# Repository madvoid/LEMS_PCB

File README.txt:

Eagle Files for LEMS PCB
Work in progress

The Mega Shield Schematic/Layout will be used as a reference in the future

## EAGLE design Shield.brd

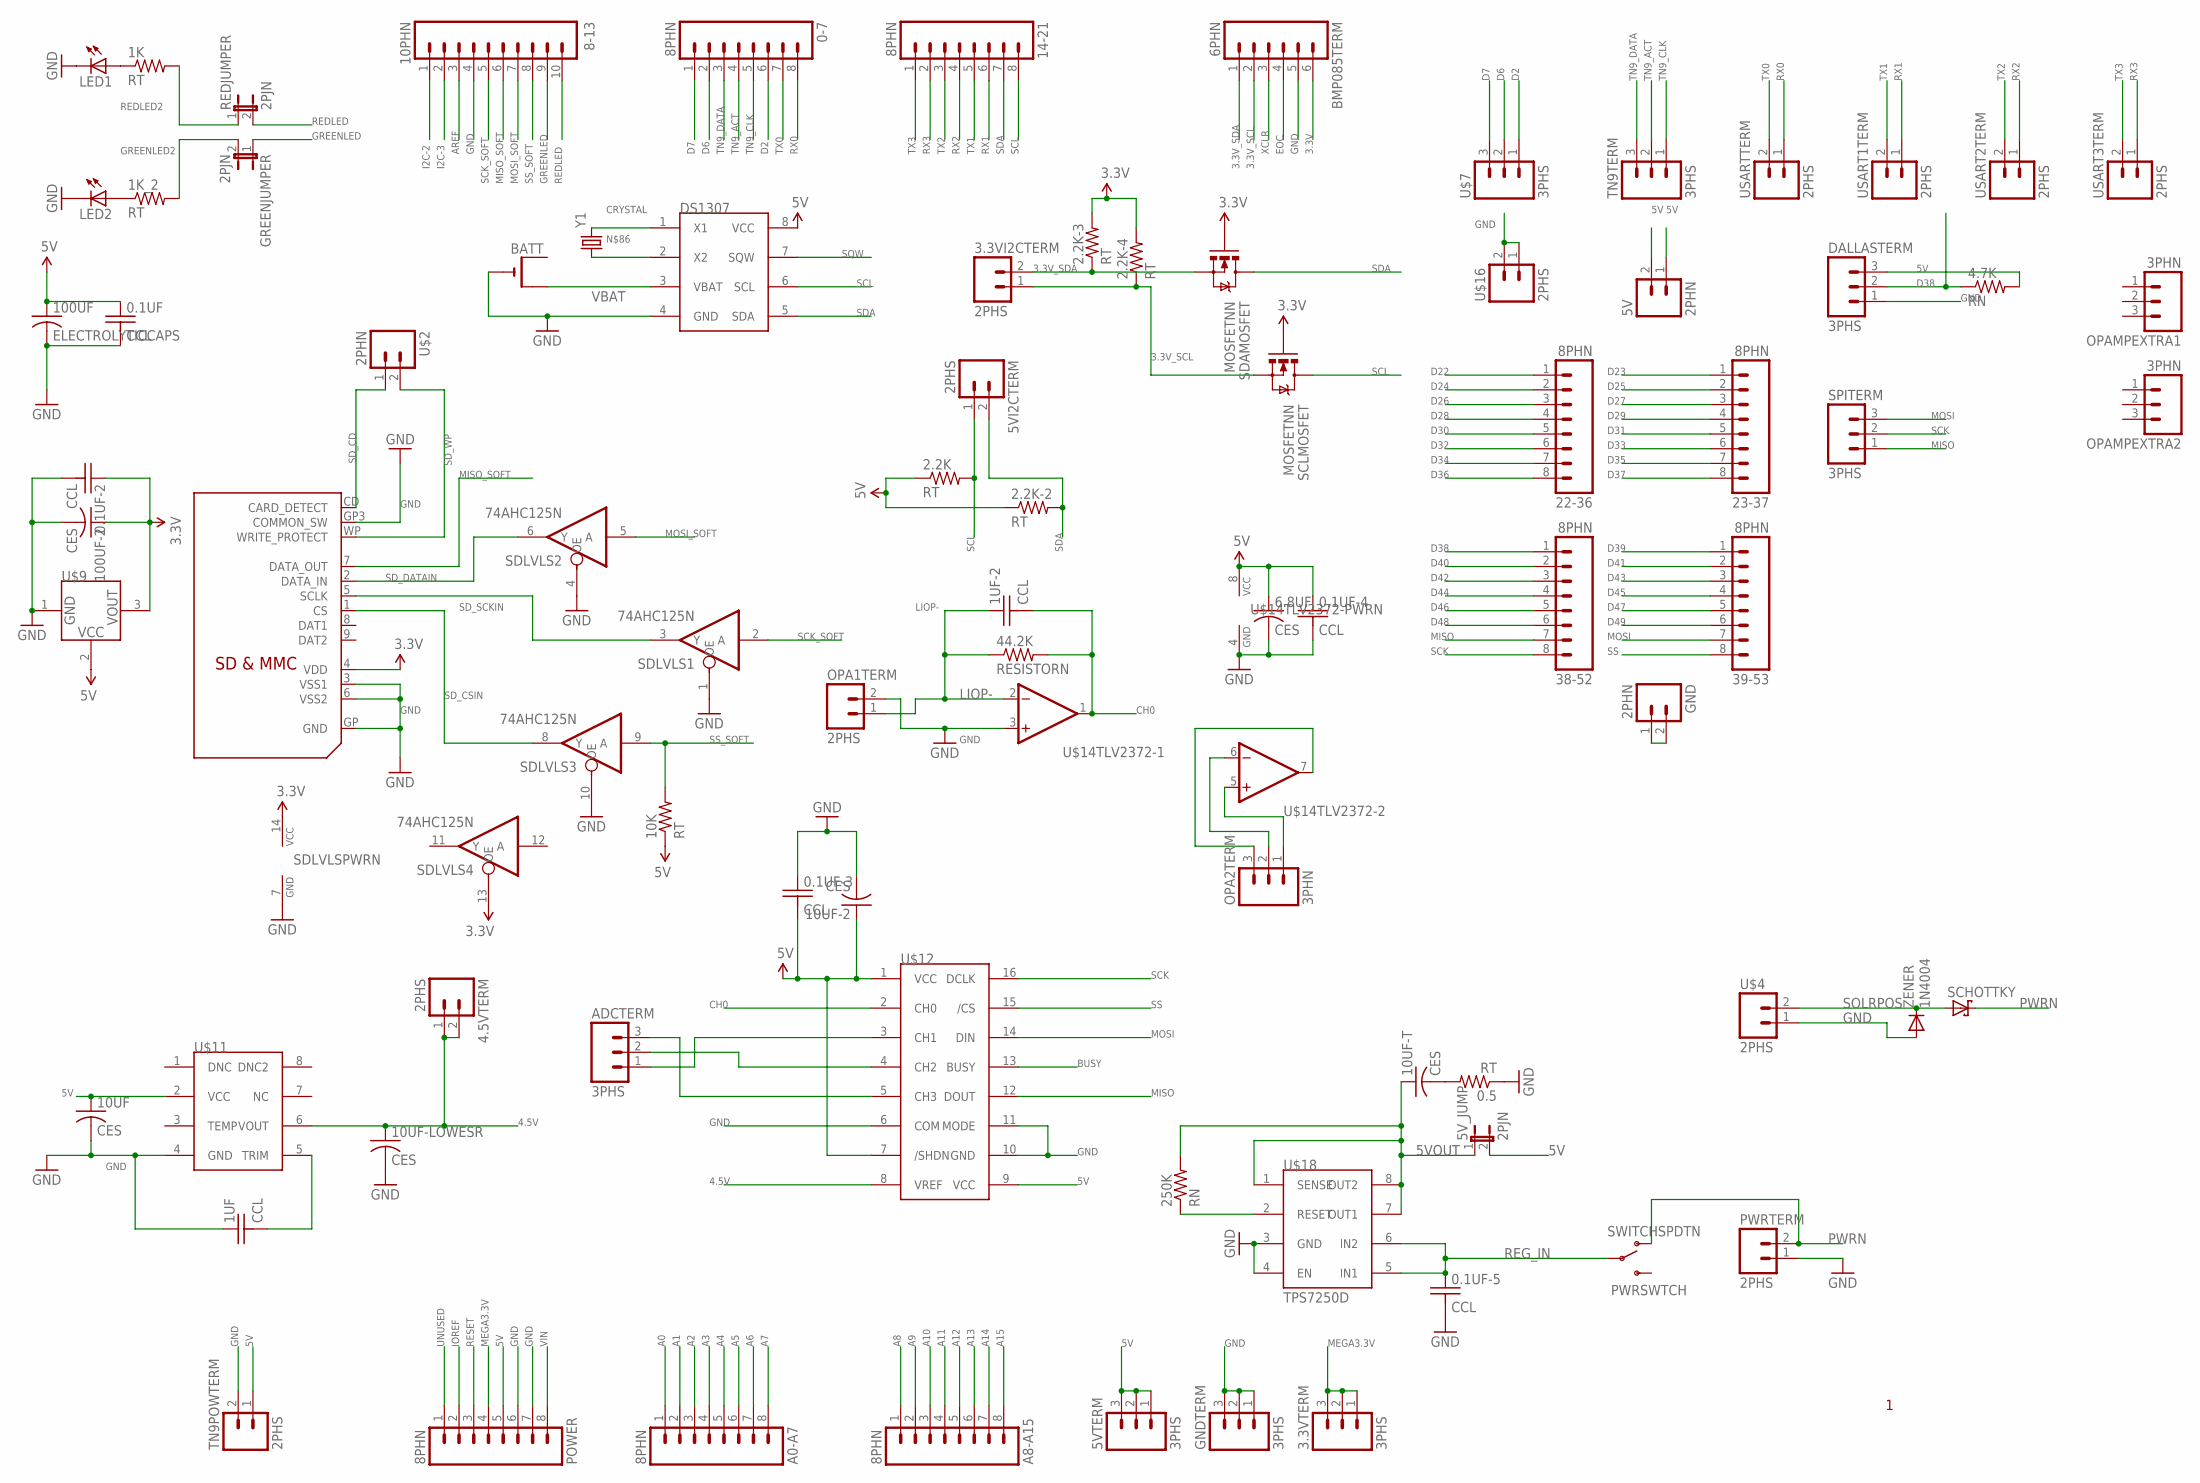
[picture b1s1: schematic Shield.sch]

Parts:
0-7, 14-21, 22-36, 23-37, 38-52, 39-53: 8PHN; 8PH
0.1UF, 0.1UF-2, 0.1UF-3, 0.1UF-4, 0.1UF-5, 1UF, 1UF-2: CCL; C025-025X050
0.5, 1K, 1K_2, 2.2K, 2.2K-2, 2.2K-3, 2.2K-4, 10K: RT; 0207/7
3.3VI2CTERM, 4.5VTERM, 5VI2CTERM: 2PHS; SCREWTERMINAL-3.5MM-2_LOCK
3.3VTERM, 5VTERM: 3PHS; SCREWTERMINAL-3.5MM-3_LOCK.007S
4.7K, 250K: RN; 0207/10
5V: 2PHN; 2PH
5V_JUMP: 2PJN; 2PH
6.8UF, 10UF, 10UF-2, 10UF-LOWESR, 10UF-T, 100UF-2: CES; E2,5-5
8-13: 10PHN; 10PH
44.2K: RESISTORN; 0207/10
100UF: ELECTROLYTICCAPS; E2,5-5
A0-A7, A8-A15: 8PHN; 8PH
ADCTERM: 3PHS; SCREWTERMINAL-3.5MM-3_LOCK.007S
BATT: CR1220THM; CR1220-THM
BMP085TERM: 6PHN; 6PH
DALLASTERM: 3PHS; SCREWTERMINAL-3.5MM-3_LOCK.007S
DS1307: DS1307P; DIL8
GND: 2PHN; 2PH
GNDTERM: 3PHS; SCREWTERMINAL-3.5MM-3_LOCK.007S
GREENJUMPER: 2PJN; 2PH
LED1, LED2: LED3MM
OPA1TERM: 2PHS; SCREWTERMINAL-3.5MM-2_LOCK
OPA2TERM: 3PHN; 3PH
OPAMPEXTRA1, OPAMPEXTRA2: 3PHN; 3PH
POWER: 8PHN; 8PH
PWRSWTCH: SWITCHSPDTN; SWITCH-SPDT
PWRTERM: 2PHS; SCREWTERMINAL-3.5MM-2_LOCK
REDJUMPER: 2PJN; 2PH
SCHOTTKY: SCHOTTKY-DIODEDO41; DO41-10
SCLMOSFET: MOSFETNN; TO-92INLINE
SDAMOSFET: MOSFETNN; TO-92INLINE
SDLVLS: 74AHC125N; DIL14
SPITERM: 3PHS; SCREWTERMINAL-3.5MM-3_LOCK.007S
TN9POWTERM: 2PHS; SCREWTERMINAL-3.5MM-2_LOCK
TN9TERM: 3PHS; SCREWTERMINAL-3.5MM-3_LOCK.007S
U$1: SDMMC06132; 06132
U$2: 2PHN; 2PH
U$4, U$16: 2PHS; SCREWTERMINAL-3.5MM-2_LOCK
U$7: 3PHS; SCREWTERMINAL-3.5MM-3_LOCK.007S
U$9: MCP1700-330T; TO-92INLINE
U$11: REF5045S; SOIC8
U$12: ADS7841P; DIL16
U$14: TLV2372P; DIL8
U$18: TPS7250D; DIL8
USART1TERM, USART2TERM, USART3TERM: 2PHS; SCREWTERMINAL-3.5MM-2_LOCK
USARTTERM: 2PHS; SCREWTERMINAL-3.5MM-2_LOCK
Y1: CRYSTALTC38H; TC38H
ZENER: 1N4004; DO41-10

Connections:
3.3V: 0.1UF-2.1, 2.2K-3.2, 2.2K-4.2, 100UF-2.+ (1), BMP085TERM.6, SCLMOSFET.2 (G), SDAMOSFET.2 (G), SDLVLS.13 (OE), SDLVLS.14 (VCC), U$1.4 (VDD), U$9.3 (VOUT)
3.3V_SCL: 2.2K-4.1, 3.3VI2CTERM.1, BMP085TERM.2, SCLMOSFET.1 (S)
3.3V_SDA: 2.2K-3.1, 3.3VI2CTERM.2, BMP085TERM.1, SDAMOSFET.1 (S)
4.5V: 4.5VTERM.1, 4.5VTERM.2, 10UF-LOWESR.+ (1), U$11.6 (VOUT), U$12.8 (VREF)
5V: 0.1UF.1, 0.1UF-3.2, 0.1UF-4.1, 2.2K.1, 2.2K-2.1, 4.7K.2, 5V.1, 5V.2, 5VTERM.1, 5VTERM.2, 5VTERM.3, 5V_JUMP.2, 6.8UF.+ (1), 10K.1, 10UF.+ (1), 10UF-2.+ (1), 100UF.+ (1), DALLASTERM.3, DS1307.8 (VCC), POWER.5, TN9POWTERM.1, U$9.2 (VCC), U$11.2 (VCC), U$12.1 (VCC), U$12.7 (/SHDN), U$12.9 (VCC), U$14.8 (VCC)
5VOUT: 5V_JUMP.1, 10UF-T.+ (1), 250K.2, U$18.1 (SENSE), U$18.7 (OUT1), U$18.8 (OUT2)
A0: A0-A7.1
A1: A0-A7.2
A2: A0-A7.3
A3: A0-A7.4
A4: A0-A7.5
A5: A0-A7.6
A6: A0-A7.7
A7: A0-A7.8
A8: A8-A15.1
A9: A8-A15.2
A10: A8-A15.3
A11: A8-A15.4
A12: A8-A15.5
A13: A8-A15.6
A14: A8-A15.7
A15: A8-A15.8
AREF: 8-13.3
BUSY: U$12.13 (BUSY)
CH0: 1UF-2.2, 44.2K.2, U$12.2 (CH0), U$14.1 (OUT)
CH1: ADCTERM.1, U$12.3 (CH1)
CH2: ADCTERM.2, U$12.4 (CH2)
CH3: ADCTERM.3, U$12.5 (CH3)
CRYSTAL: DS1307.1 (X1), Y1.2
D2: 0-7.6, U$7.1
D6: 0-7.2, U$7.2
D7: 0-7.1, U$7.3
D22: 22-36.1
D23: 23-37.1
D24: 22-36.2
D25: 23-37.2
D26: 22-36.3
D27: 23-37.3
D28: 22-36.4
D29: 23-37.4
D30: 22-36.5
D31: 23-37.5
D32: 22-36.6
D33: 23-37.6
D34: 22-36.7
D35: 23-37.7
D36: 22-36.8
D37: 23-37.8
D38: 4.7K.1, 38-52.1, DALLASTERM.2
D39: 39-53.1
D40: 38-52.2
D41: 39-53.2
D42: 38-52.3
D43: 39-53.3
D44: 38-52.4
D45: 39-53.4
D46: 38-52.5
D47: 39-53.5
D48: 38-52.6
D49: 39-53.6
EOC: BMP085TERM.4
GND: 0.1UF.2, 0.1UF-2.2, 0.1UF-3.1, 0.1UF-4.2, 0.1UF-5.2, 0.5.1, 1UF.1, 6.8UF.- (2), 8-13.4, 10UF.- (2), 10UF-2.- (2), 10UF-LOWESR.- (2), 100UF.- (2), 100UF-2.- (2), BATT.-, BMP085TERM.5, DALLASTERM.1, DS1307.4 (GND), GNDTERM.1, GNDTERM.2, GNDTERM.3, LED1.K (C), LED2.K (C), OPA1TERM.2, POWER.6, POWER.7, PWRTERM.1, SDLVLS.1 (OE), SDLVLS.4 (OE), SDLVLS.7 (GND), SDLVLS.10 (OE), TN9POWTERM.2, U$1.3 (VSS1), U$1.6 (VSS2), U$1.GP (GND), U$1.GP3 (COMMON_SW), U$4.1, U$9.1 (GND), U$11.4 (GND), U$12.6 (COM), U$12.10 (GND), U$12.11 (MODE), U$14.3 (+IN), U$14.4 (GND), U$16.1, U$16.2, U$18.3 (GND), U$18.4 (EN), ZENER.A
GREENLED: 8-13.9, GREENJUMPER.1
GREENLED2: 1K_2.2, GREENJUMPER.2
I2C-2: 8-13.1
I2C-3: 8-13.2
IOREF: POWER.2
LIOP-: 1UF-2.1, 44.2K.1, OPA1TERM.1, U$14.2 (-IN)
MEGA3.3V: 3.3VTERM.1, 3.3VTERM.2, 3.3VTERM.3, POWER.4
MISO: 38-52.7, SPITERM.1, U$12.12 (DOUT)
MISO_SOFT: 8-13.6, U$1.7 (DATA_OUT)
MOSI: 39-53.7, SPITERM.3, U$12.14 (DIN)
MOSI_SOFT: 8-13.7, SDLVLS.5 (A)
unnamed: 1UF.2, U$11.5 (TRIM)
unnamed: OPA2TERM.1, U$14.5 (+IN)
unnamed: OPA2TERM.2, U$14.6 (-IN)
unnamed: OPA2TERM.3, U$14.7 (OUT)
unnamed: GND.1, GND.2
unnamed: 250K.1, U$18.2 (RESET)
unnamed: 0.5.2, 10UF-T.- (2)
unnamed: 1K.1, LED1.A
unnamed: 1K_2.1, LED2.A
unnamed: DS1307.2 (X2), Y1.1
PWRN: PWRSWTCH.1 (O), PWRTERM.2, SCHOTTKY.C
REDLED: 8-13.10, REDJUMPER.2
REDLED2: 1K.2, REDJUMPER.1
REG_IN: 0.1UF-5.1, PWRSWTCH.2, U$18.5 (IN1), U$18.6 (IN2)
RESET: POWER.3
RX0: 0-7.8, USARTTERM.1
RX1: 14-21.6, USART1TERM.1
RX2: 14-21.4, USART2TERM.1
RX3: 14-21.2, USART3TERM.1
SCK: 38-52.8, SPITERM.2, U$12.16 (DCLK)
SCK_SOFT: 8-13.5, SDLVLS.2 (A)
SCL: 2.2K.2, 5VI2CTERM.1, 14-21.8, DS1307.6 (SCL), SCLMOSFET.3 (D)
SDA: 2.2K-2.2, 5VI2CTERM.2, 14-21.7, DS1307.5 (SDA), SDAMOSFET.3 (D)
SD_CD: U$1.CD (CARD_DETECT), U$2.1
SD_CSIN: SDLVLS.8 (Y), U$1.1 (CS)
SD_DATAIN: SDLVLS.6 (Y), U$1.2 (DATA_IN)
SD_SCKIN: SDLVLS.3 (Y), U$1.5 (SCLK)
SD_WP: U$1.WP (WRITE_PROTECT), U$2.2
SOLRPOS: SCHOTTKY.A, U$4.2, ZENER.C
SQW: DS1307.7 (SQW)
SS: 39-53.8, U$12.15 (/CS)
SS_SOFT: 8-13.8, 10K.2, SDLVLS.9 (A)
TN9_ACT: 0-7.4, TN9TERM.2
TN9_CLK: 0-7.5, TN9TERM.1
TN9_DATA: 0-7.3, TN9TERM.3
TX0: 0-7.7, USARTTERM.2
TX1: 14-21.5, USART1TERM.2
TX2: 14-21.3, USART2TERM.2
TX3: 14-21.1, USART3TERM.2
UNUSED: POWER.1
VBAT: BATT.+2 (+1), DS1307.3 (VBAT)
VIN: POWER.8
XCLR: BMP085TERM.3

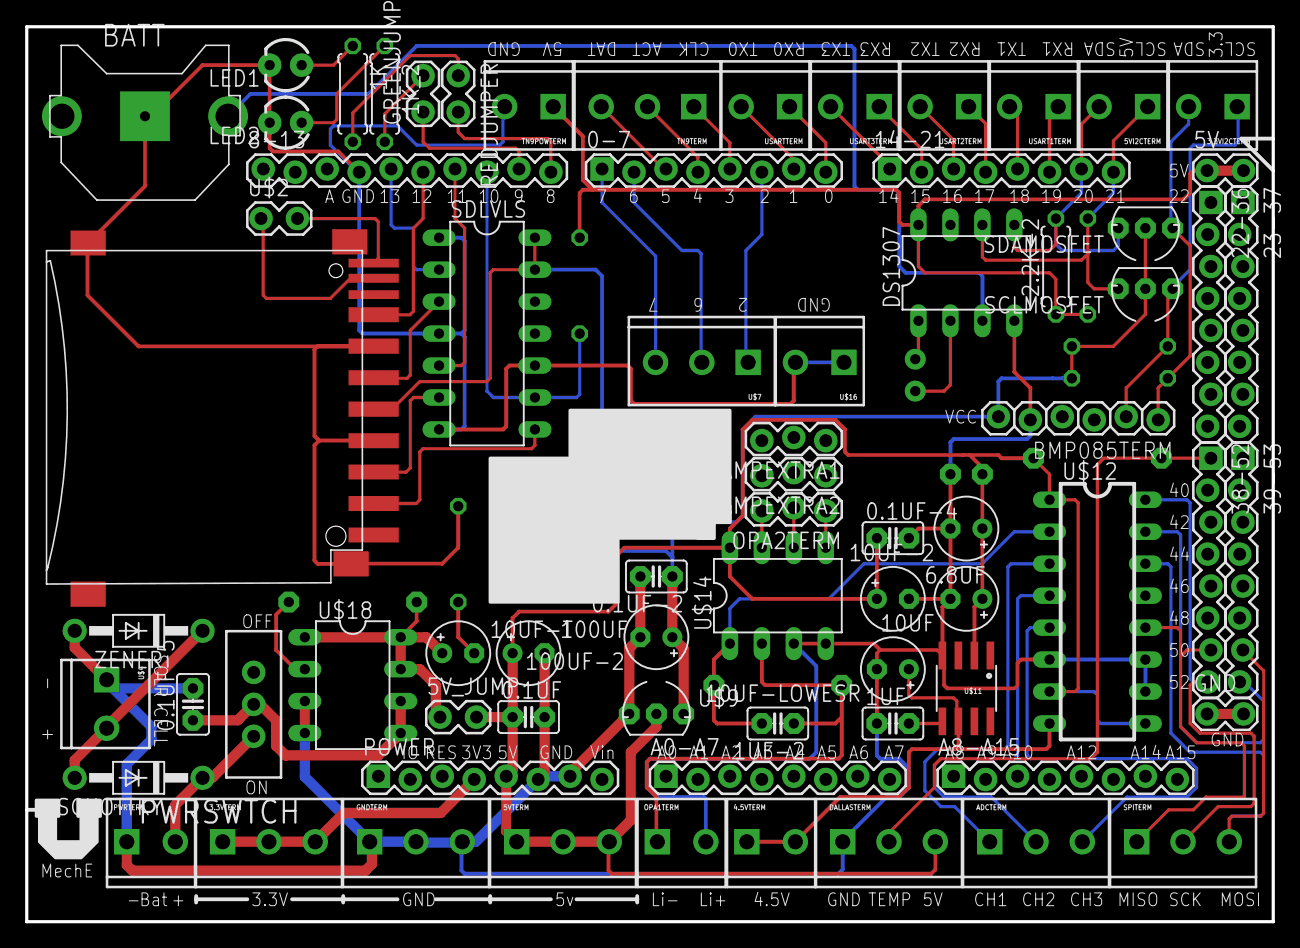
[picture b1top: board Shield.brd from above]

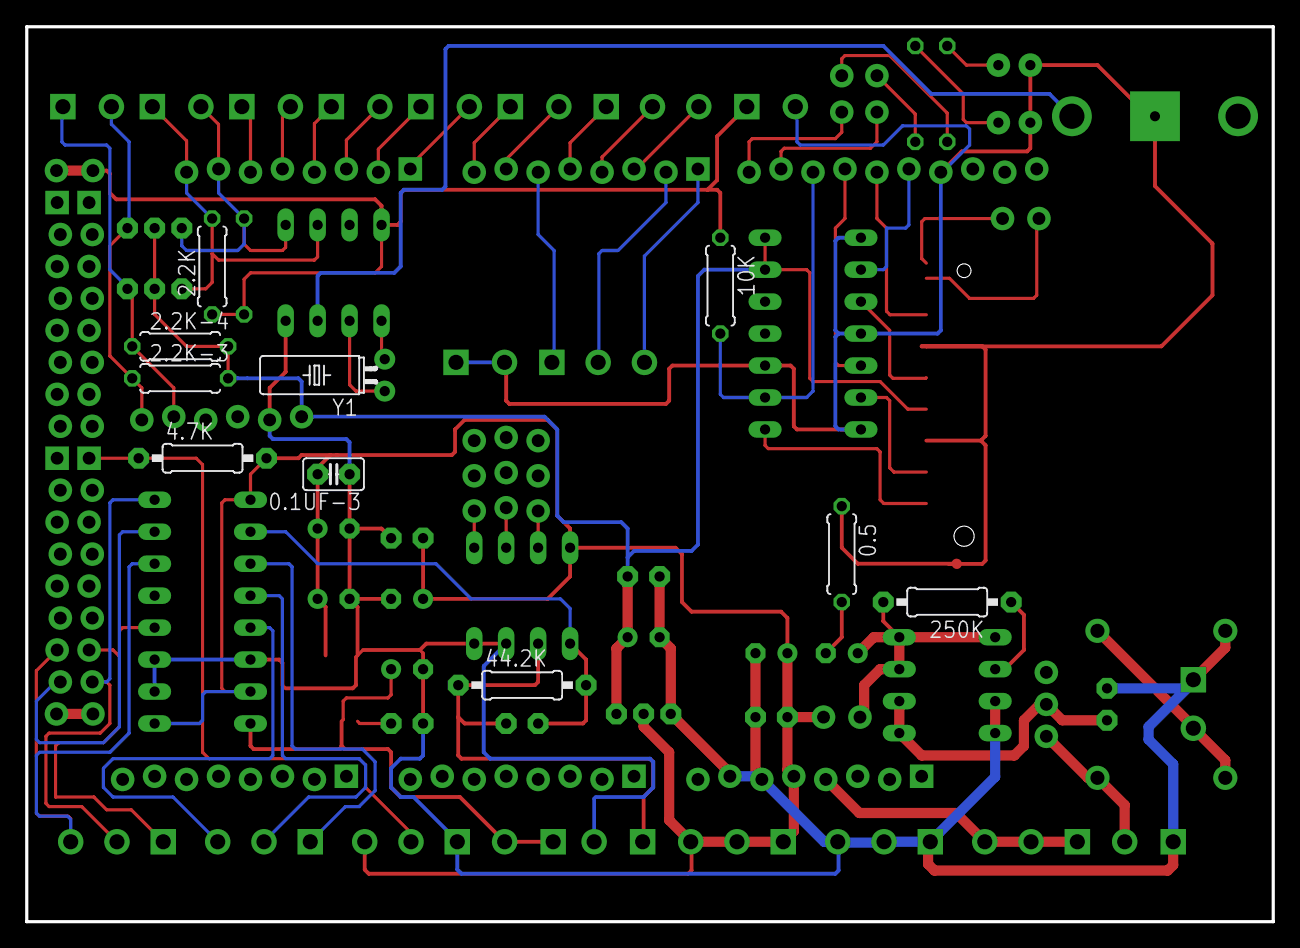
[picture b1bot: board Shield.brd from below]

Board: 2 copper layers, 99.1 x 71.1 mm, 82 parts (10 on the bottom side), 62 nets.

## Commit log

2012-05-08 Added Mega Shield reference and various components
2012-05-15 Adding Eagle Backups
2012-05-16 Added SD Card Circuit
2012-05-16 Added names and various details
2012-05-17 Added 4.5V Reference
2012-05-17 Added ADS7841
2012-05-18 First Complete Schematic
2012-05-18 Added board
2012-05-18 All components on board
2012-05-22 Started Routing
2012-05-22 Improved Routing
2012-05-22 Continued routing
2012-05-23 Almost complete routing
2012-05-23 First completed routing
2012-05-23 Final before GERBER files
2012-05-23 Added Gerber Files
2012-06-04 Added Soldering Order List
2012-06-13 Beginning Board Revision 2
2012-06-13 Still need to finalize power components
2012-06-14 Complete Prototype #2
2012-06-20 Started Revision 3
2012-06-21 About to add charging circuit
2012-06-21 Added everything but power, charging, and various silkscreen
2012-06-22 Added charging circuit to schematic
2012-06-22 Changed charging circuit, finished routing
2012-06-22 Ready to create gerber files for Mk2
2012-06-26 Added middle screw terminals
2012-06-29 Added marking area
2012-07-06 Minor Spacing Changes
2012-08-28 Ready for Quantity Manufacturing

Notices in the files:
parts and their libraries:
SparkFun-Aesthetics: Licensing: CC v3.0 Share-Alike You are welcome to use this library for commercial purposes.
